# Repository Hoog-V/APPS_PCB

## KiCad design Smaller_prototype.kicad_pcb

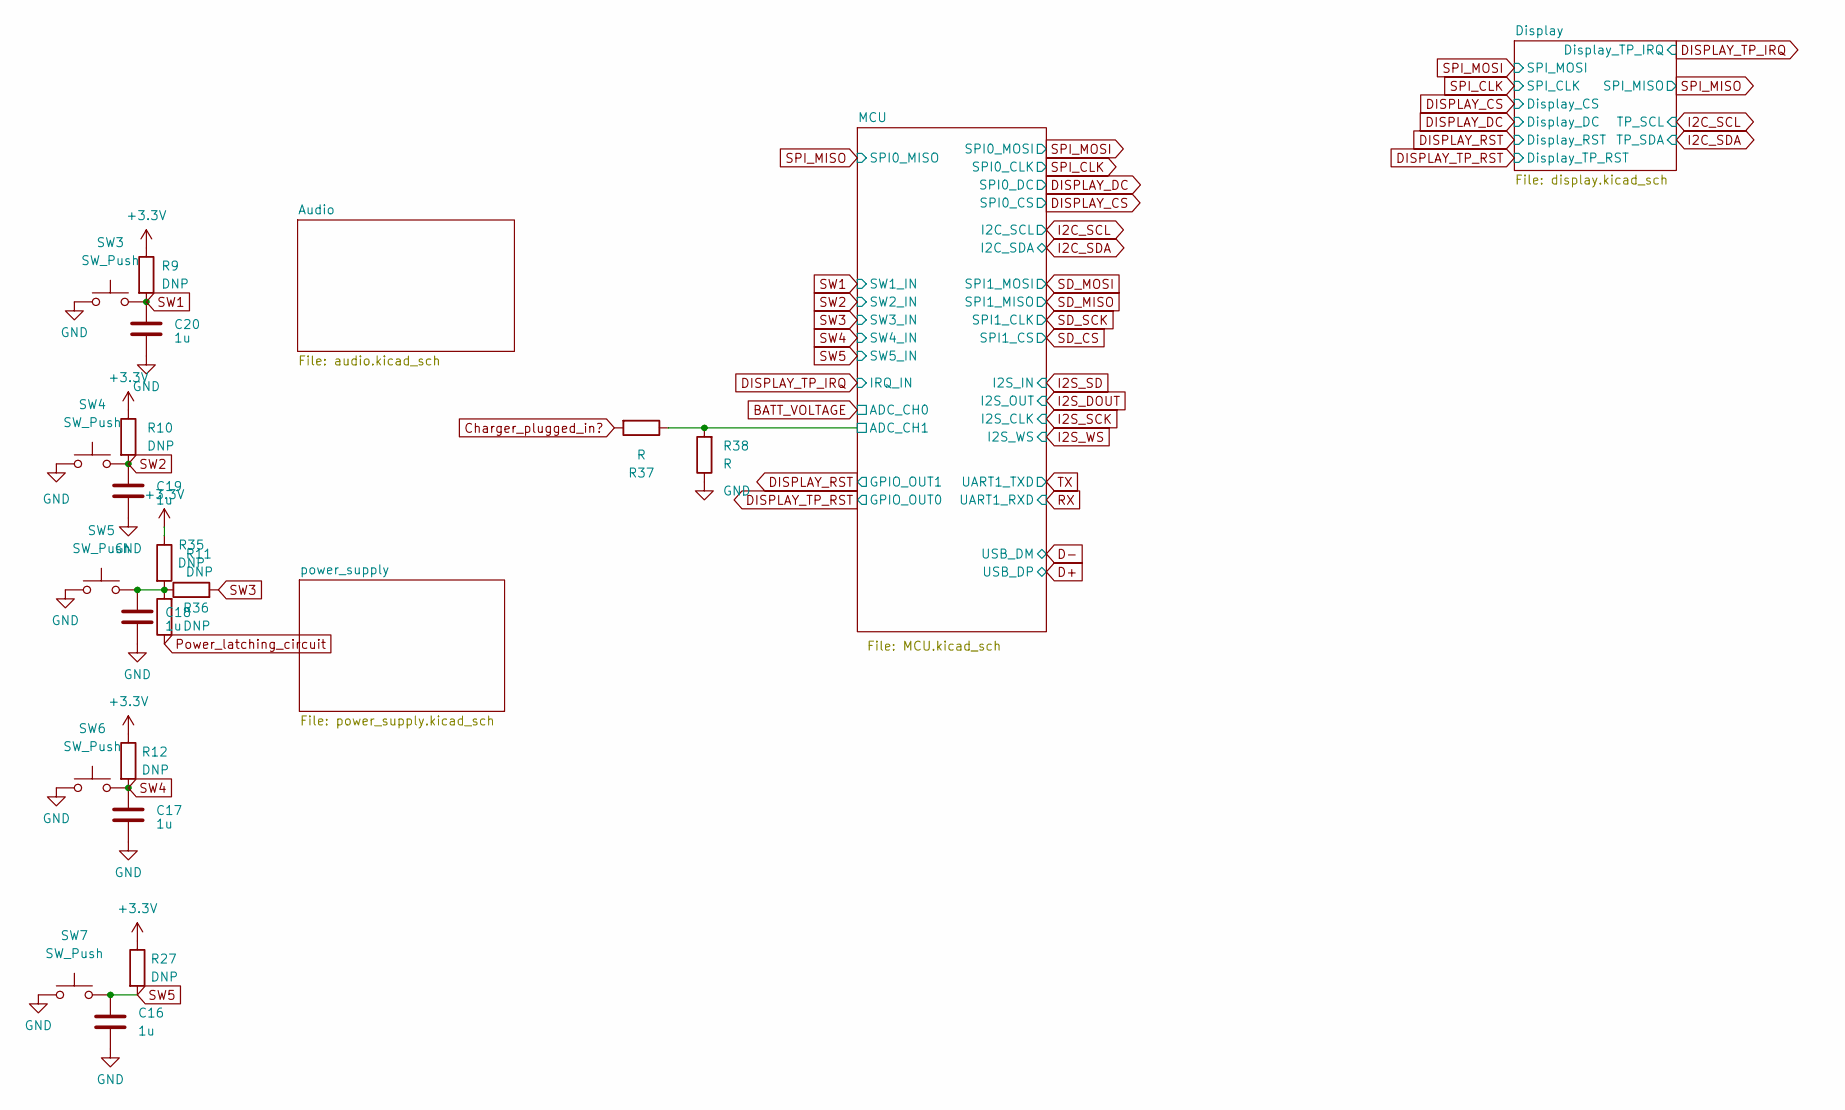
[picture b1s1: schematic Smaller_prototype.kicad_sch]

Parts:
C16, C17, C18, C19, C20: 1u; C_0603_1608Metric_Pad1.08x0.95mm_HandSolder
R9, R10, R11, R12, R27, R35, R36: DNP; R_0603_1608Metric_Pad0.98x0.95mm_HandSolder
R37, R38: R; R_0603_1608Metric_Pad0.98x0.95mm_HandSolder
SW3, SW4, SW5, SW6, SW7: SW_Push; SW_SPST_B3S-1000

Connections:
+3.3V: R9.1, R10.1, R11.1, R12.1, R27.1; also elsewhere on the board
/MCU/ADC_CH1: R37.1, R38.2; also elsewhere on the board
Charger_plugged_in?: R37.2; also elsewhere on the board
GND: C16.2, C17.2, C18.2, C19.2, C20.2, R38.1, SW3.1, SW4.1, SW5.1, SW6.1, SW7.1; also elsewhere on the board
unnamed: C18.1, R11.2, R35.1, R36.2, SW5.2
Power_latching_circuit: R36.1; also elsewhere on the board
SW1: C20.1, R9.2, SW3.2; also elsewhere on the board
SW2: C19.1, R10.2, SW4.2; also elsewhere on the board
SW3: R35.2; also elsewhere on the board
SW4: C17.1, R12.2, SW6.2; also elsewhere on the board
SW5: C16.1, R27.2, SW7.2; also elsewhere on the board

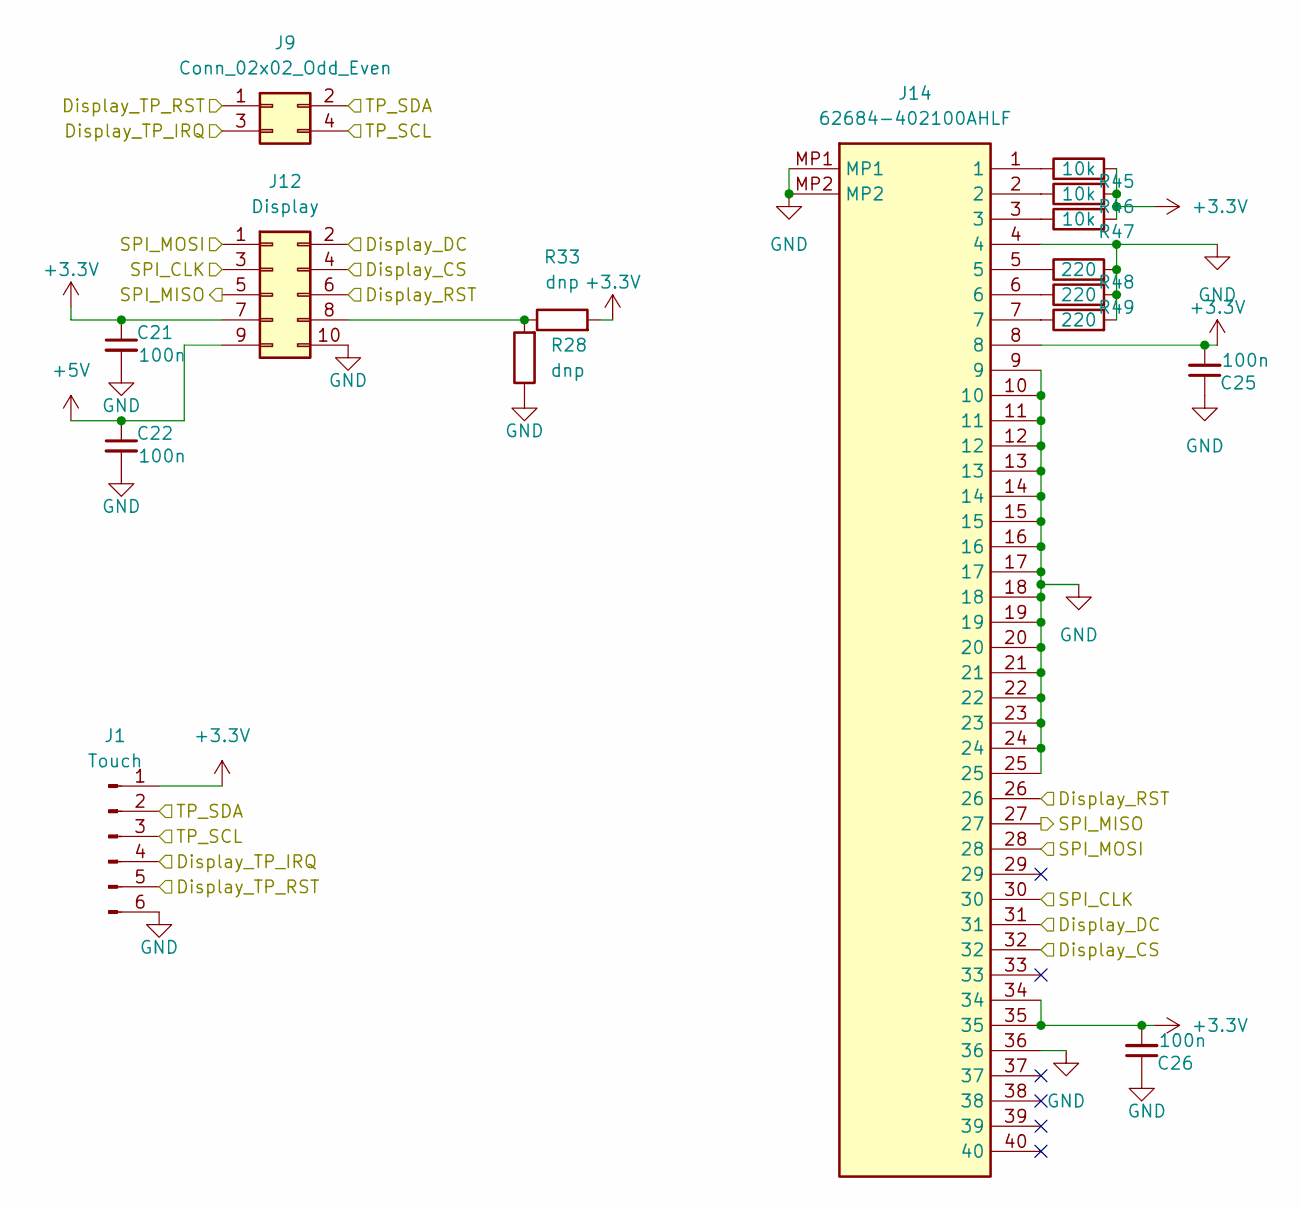
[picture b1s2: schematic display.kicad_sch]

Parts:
C21, C22, C25, C26: 100n; C_0603_1608Metric_Pad1.08x0.95mm_HandSolder
J1: Touch; TE_0-1734839-6_1x06-1MP_P0.5mm_Horizontal
J9: Conn_02x02_Odd_Even; PinHeader_2x02_P2.54mm_Vertical_SMD
J12: Display; PinHeader_2x05_P2.54mm_Vertical_SMD
J14: 62684-402100AHLF; 62684402100AHLF; Manufacturer_Part_Number 62684-402100AHLF
R28, R33: dnp; R_0603_1608Metric_Pad0.98x0.95mm_HandSolder
R45, R46, R47: 10k; R_0603_1608Metric_Pad0.98x0.95mm_HandSolder
R48, R49, R50: 220; R_0603_1608Metric_Pad0.98x0.95mm_HandSolder

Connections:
+3.3V: C21.1, C25.2, C26.2, J1.1, J12.7, J14.8, J14.34, J14.35, R33.2, R45.2, R46.2, R47.2; also elsewhere on the board
+5V: C22.1, J12.9; also elsewhere on the board
DISPLAY_CS: J12.4, J14.32; also elsewhere on the board
DISPLAY_DC: J12.2, J14.31; also elsewhere on the board
DISPLAY_RST: J12.6, J14.26; also elsewhere on the board
DISPLAY_TP_IRQ: J1.4, J9.3; also elsewhere on the board
DISPLAY_TP_RST: J1.5, J9.1; also elsewhere on the board
GND: C21.2, C22.2, C25.1, C26.1, J1.6, J12.10, J14.4, J14.9, J14.10, J14.11, J14.12, J14.13, J14.14, J14.15, J14.16, J14.17, J14.18, J14.19, J14.20, J14.21, J14.22, J14.23, J14.24, J14.25, J14.36, J14.MP1, J14.MP2, R28.1, R48.2, R49.2, R50.2; also elsewhere on the board
I2C_SCL: J1.3, J9.4; also elsewhere on the board
I2C_SDA: J1.2, J9.2; also elsewhere on the board
unnamed: J12.8, R28.2, R33.1
unnamed: J14.1, R45.1
unnamed: J14.2, R46.1
unnamed: J14.3, R47.1
unnamed: J14.5, R48.1
unnamed: J14.6, R49.1
unnamed: J14.7, R50.1
SPI_CLK: J12.3, J14.30; also elsewhere on the board
SPI_MISO: J12.5, J14.27; also elsewhere on the board
SPI_MOSI: J12.1, J14.28; also elsewhere on the board

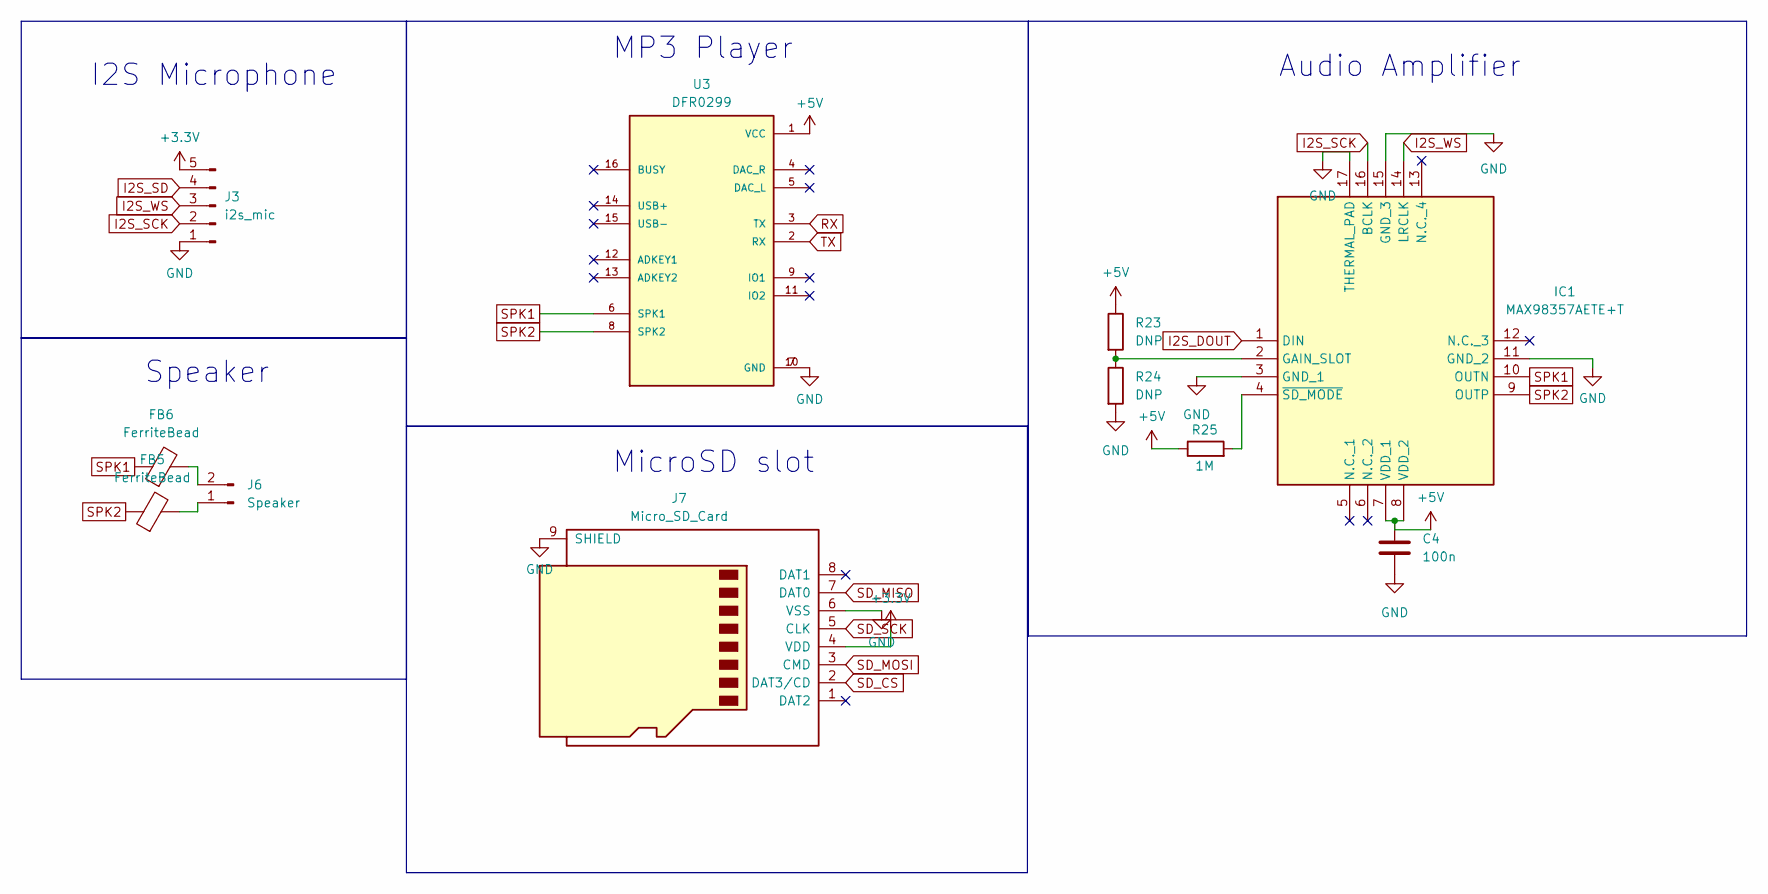
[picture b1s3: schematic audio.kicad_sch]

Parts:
C4: 100n; C_0603_1608Metric_Pad1.08x0.95mm_HandSolder
FB5, FB6: FerriteBead; R_1812_4532Metric
IC1: MAX98357AETE+T; QFN50P300X300X80-17N; Mouser Part Number 700-MAX98357AETE+T
J3: i2s_mic; PinHeader_1x05_P2.54mm_Vertical
J6: Speaker; PinHeader_1x02_P2.54mm_Vertical
J7: Micro_SD_Card; microSD_HC_Molex_47219-2001
R23, R24: DNP; R_0603_1608Metric_Pad0.98x0.95mm_HandSolder
R25: 1M; R_0603_1608Metric_Pad0.98x0.95mm_HandSolder
U3: DFR0299; DFPlayer_V2

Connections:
+3.3V: J3.5, J7.4 (VDD); also elsewhere on the board
+5V: C4.1, IC1.7 (VDD_1), IC1.8 (VDD_2), R23.1, R25.1, U3.1 (VCC); also elsewhere on the board
GND: C4.2, IC1.3 (GND_1), IC1.11 (GND_2), IC1.15 (GND_3), IC1.17 (THERMAL_PAD), J3.1, J7.6 (VSS), J7.9 (SHIELD), R24.2, U3.7 (GND), U3.10 (GND); also elsewhere on the board
I2S_DOUT: IC1.1 (DIN); also elsewhere on the board
I2S_SCK: IC1.16 (BCLK), J3.2; also elsewhere on the board
I2S_SD: J3.4; also elsewhere on the board
I2S_WS: IC1.14 (LRCLK), J3.3; also elsewhere on the board
unnamed: IC1.2 (GAIN_SLOT), R23.2, R24.1
unnamed: IC1.4 (~SD_MODE), R25.2
unnamed: FB5.2, J6.1
unnamed: FB6.2, J6.2
RX: U3.3 (TX); also elsewhere on the board
SD_CS: J7.2 (DAT3/CD); also elsewhere on the board
SD_MISO: J7.7 (DAT0); also elsewhere on the board
SD_MOSI: J7.3 (CMD); also elsewhere on the board
SD_SCK: J7.5 (CLK); also elsewhere on the board
SPK1: FB6.1, IC1.10 (OUTN), U3.6 (SPK1)
SPK2: FB5.1, IC1.9 (OUTP), U3.8 (SPK2)
TX: U3.2 (RX); also elsewhere on the board

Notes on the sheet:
Speaker
MP3 Player
I2S Microphone
Audio Amplifier
MicroSD slot

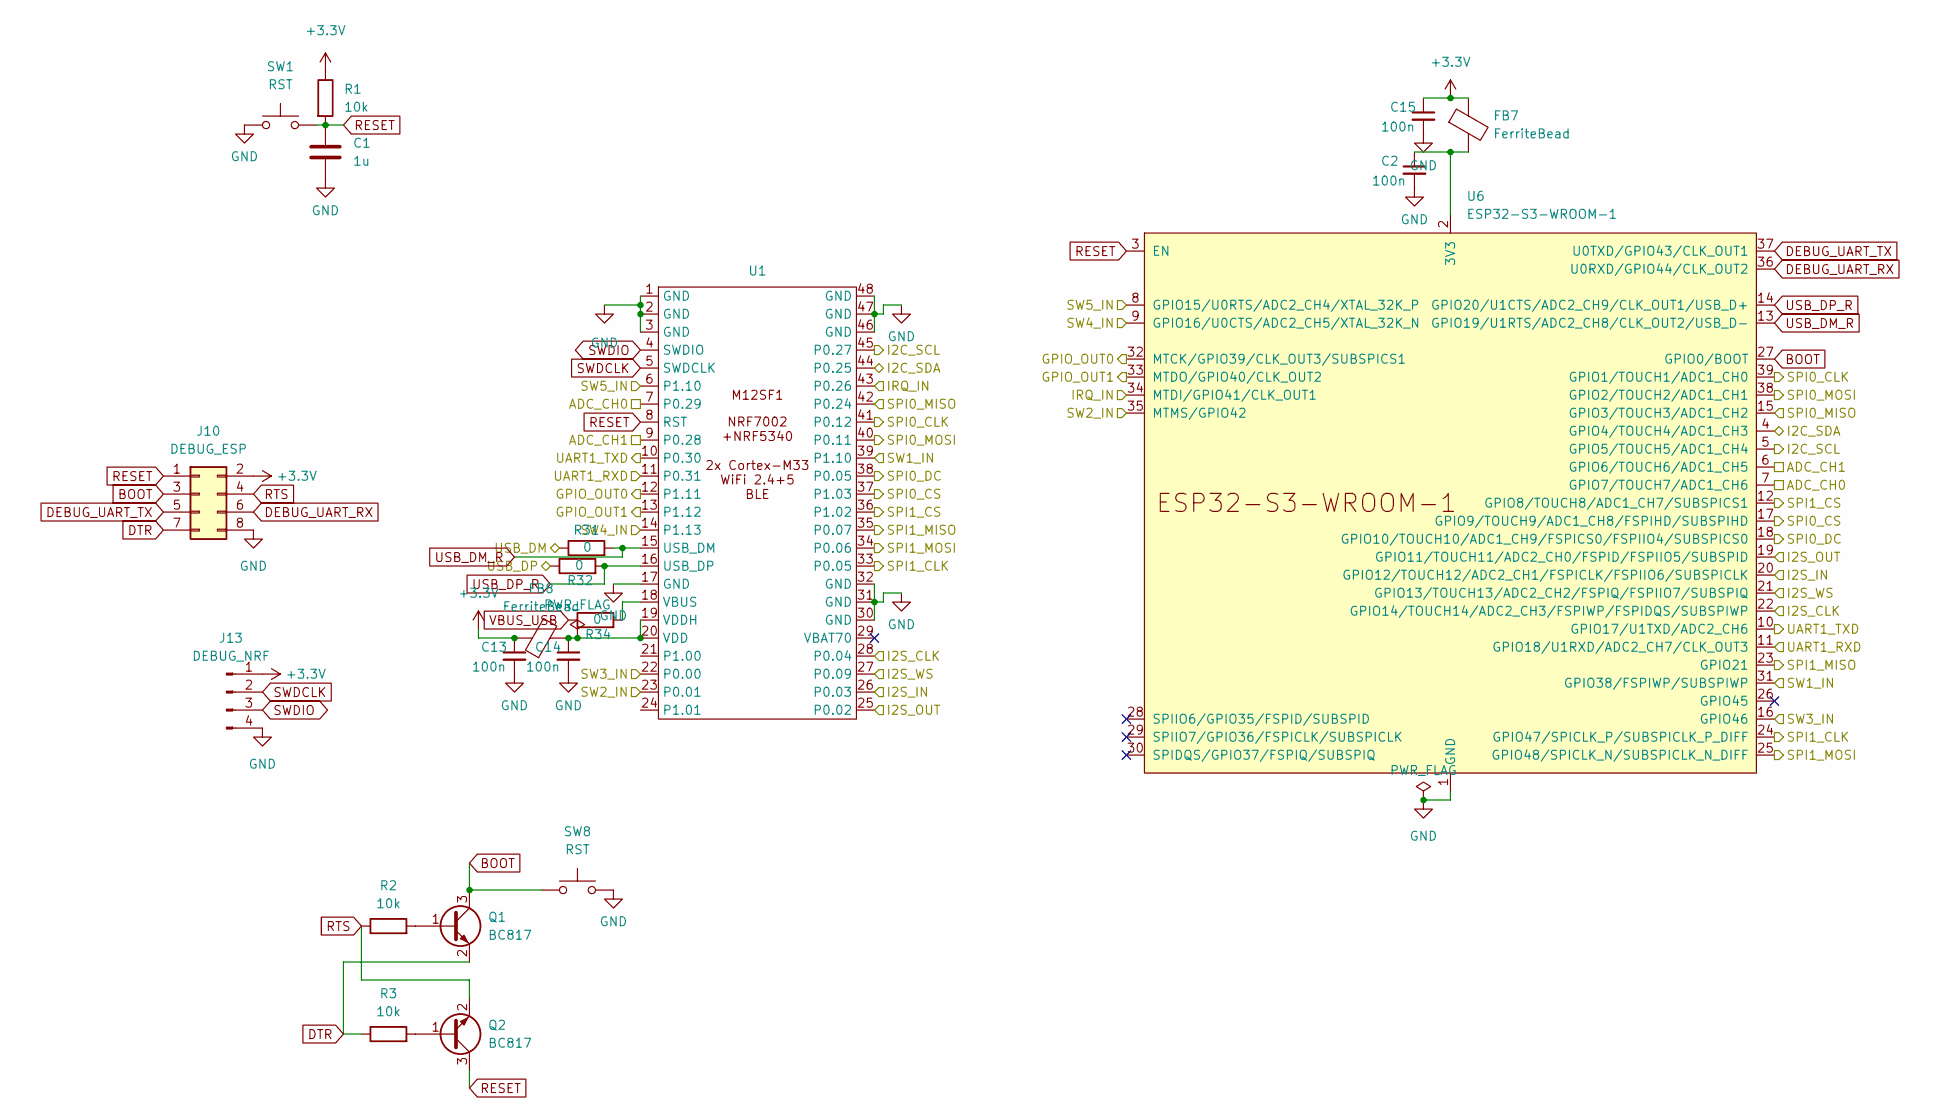
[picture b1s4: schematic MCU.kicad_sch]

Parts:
C1: 1u; C_0603_1608Metric_Pad1.08x0.95mm_HandSolder
C2, C13, C14, C15: 100n; C_0603_1608Metric_Pad1.08x0.95mm_HandSolder
FB7, FB8: FerriteBead; R_1812_4532Metric
J10: DEBUG_ESP; PinHeader_2x04_P2.54mm_Vertical_SMD
J13: DEBUG_NRF; PinHeader_2x02_P2.54mm_Vertical_SMD
Q1, Q2: BC817; SOT-23
R1, R2, R3: 10k; R_0603_1608Metric_Pad0.98x0.95mm_HandSolder
R31, R32, R34: 0; R_0603_1608Metric_Pad0.98x0.95mm_HandSolder
SW1, SW8: RST; SW_SPST_B3S-1000
U1: M12SF1
U6: ESP32-S3-WROOM-1

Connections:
+3.3V: C13.1, C15.1, FB7.1, FB8.1, J10.2, J13.1, R1.1; also elsewhere on the board
/MCU/ADC_CH1: U1.9 (P0.28), U6.6 (GPIO6/TOUCH6/ADC1_CH5); also elsewhere on the board
BATT_VOLTAGE: U1.7 (P0.29), U6.7 (GPIO7/TOUCH7/ADC1_CH6); also elsewhere on the board
BOOT: J10.3, Q1.3 (C), SW8.1, U6.27 (GPIO0/BOOT)
D+: R32.1; also elsewhere on the board
D-: R31.1; also elsewhere on the board
DEBUG_UART_RX: J10.6, U6.36 (U0RXD/GPIO44/CLK_OUT2)
DEBUG_UART_TX: J10.5, U6.37 (U0TXD/GPIO43/CLK_OUT1)
DISPLAY_CS: U1.37 (P1.03), U6.17 (GPIO9/TOUCH9/ADC1_CH8/FSPIHD/SUBSPIHD); also elsewhere on the board
DISPLAY_DC: U1.38 (P0.05), U6.18 (GPIO10/TOUCH10/ADC1_CH9/FSPICS0/FSPIIO4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); also elsewhere on the board
DISPLAY_RST: U1.13 (P1.12), U6.33 (MTDO/GPIO40/CLK_OUT2); also elsewhere on the board
DISPLAY_TP_IRQ: U1.43 (P0.26), U6.34 (MTDI/GPIO41/CLK_OUT1); also elsewhere on the board
DISPLAY_TP_RST: U1.12 (P1.11), U6.32 (MTCK/GPIO39/CLK_OUT3/SUBSPICS1); also elsewhere on the board
DTR: J10.7, Q1.2 (E), R3.1
GND: C1.2, C2.2, C13.2, C14.2, C15.2, J10.8, J13.4, SW1.1, SW8.2, U1.1 (GND), U1.2 (GND), U1.3 (GND), U1.17 (GND), U1.30 (GND), U1.31 (GND), U1.32 (GND), U1.46 (GND), U1.47 (GND), U1.48 (GND), U6.1 (GND), U6.40 (GND), U6.41 (GND); also elsewhere on the board
I2C_SCL: U1.45 (P0.27), U6.5 (GPIO5/TOUCH5/ADC1_CH4); also elsewhere on the board
I2C_SDA: U1.44 (P0.25), U6.4 (GPIO4/TOUCH4/ADC1_CH3); also elsewhere on the board
I2S_DOUT: U1.25 (P0.02), U6.19 (GPIO11/TOUCH11/ADC2_CH0/FSPID/FSPIIO5/S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); also elsewhere on the board
I2S_SCK: U1.28 (P0.04), U6.22 (GPIO14/TOUCH14/ADC2_CH3/FSPIWP/FSPIDQS/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); also elsewhere on the board
I2S_SD: U1.26 (P0.03), U6.20 (GPIO12/TOUCH12/ADC2_CH1/FSPICLK/FSPIIO6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); also elsewhere on the board
I2S_WS: U1.27 (P0.09), U6.21 (GPIO13/TOUCH13/ADC2_CH2/FSPIQ/FSPIIO7/S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); also elsewhere on the board
unnamed: Q1.1 (B), R2.2
unnamed: Q2.1 (B), R3.2
unnamed: R34.2, U1.18 (VBUS)
unnamed: C14.1, FB8.2, U1.19 (VDDH), U1.20 (VDD)
unnamed: C2.1, FB7.2, U6.2 (3V3)
RESET: C1.1, J10.1, Q2.3 (C), R1.2, SW1.2, U1.8 (RST), U6.3 (EN)
RTS: J10.4, Q2.2 (E), R2.1
RX: U1.11 (P0.31), U6.11 (GPIO18/U1RXD/ADC2_CH7/CLK_OUT3); also elsewhere on the board
SD_CS: U1.36 (P1.02), U6.12 (GPIO8/TOUCH8/ADC1_CH7/SUBSPICS1); also elsewhere on the board
SD_MISO: U1.35 (P0.07), U6.23 (GPIO21); also elsewhere on the board
SD_MOSI: U1.34 (P0.06), U6.25 (GPIO48/SPICLK_N/SUBSPICLK_N_DIFF); also elsewhere on the board
SD_SCK: U1.33 (P0.05), U6.24 (GPIO47/SPICLK_P/SUBSPICLK_P_DIFF); also elsewhere on the board
SPI_CLK: U1.41 (P0.12), U6.39 (GPIO1/TOUCH1/ADC1_CH0); also elsewhere on the board
SPI_MISO: U1.42 (P0.24), U6.15 (GPIO3/TOUCH3/ADC1_CH2); also elsewhere on the board
SPI_MOSI: U1.40 (P0.11), U6.38 (GPIO2/TOUCH2/ADC1_CH1); also elsewhere on the board
SW1: U1.39 (P1.10), U6.31 (GPIO38/FSPIWP/SUBSPIWP); also elsewhere on the board
SW2: U1.23 (P0.01), U6.35 (MTMS/GPIO42); also elsewhere on the board
SW3: U1.22 (P0.00), U6.16 (GPIO46); also elsewhere on the board
SW4: U1.14 (P1.13), U6.9 (GPIO16/U0CTS/ADC2_CH5/XTAL_32K_N); also elsewhere on the board
SW5: U1.6 (P1.10), U6.8 (GPIO15/U0RTS/ADC2_CH4/XTAL_32K_P); also elsewhere on the board
SWDCLK: J13.2, U1.5 (SWDCLK)
SWDIO: J13.3, U1.4 (SWDIO)
TX: U1.10 (P0.30), U6.10 (GPIO17/U1TXD/ADC2_CH6); also elsewhere on the board
USB_DM_R: R31.2, U1.15 (USB_DM), U6.13 (GPIO19/U1RTS/ADC2_CH8/CLK_OUT2/USB_D-)
USB_DP_R: R32.2, U1.16 (USB_DP), U6.14 (GPIO20/U1CTS/ADC2_CH9/CLK_OUT1/USB_D+)
VBUS_USB: R34.1; also elsewhere on the board

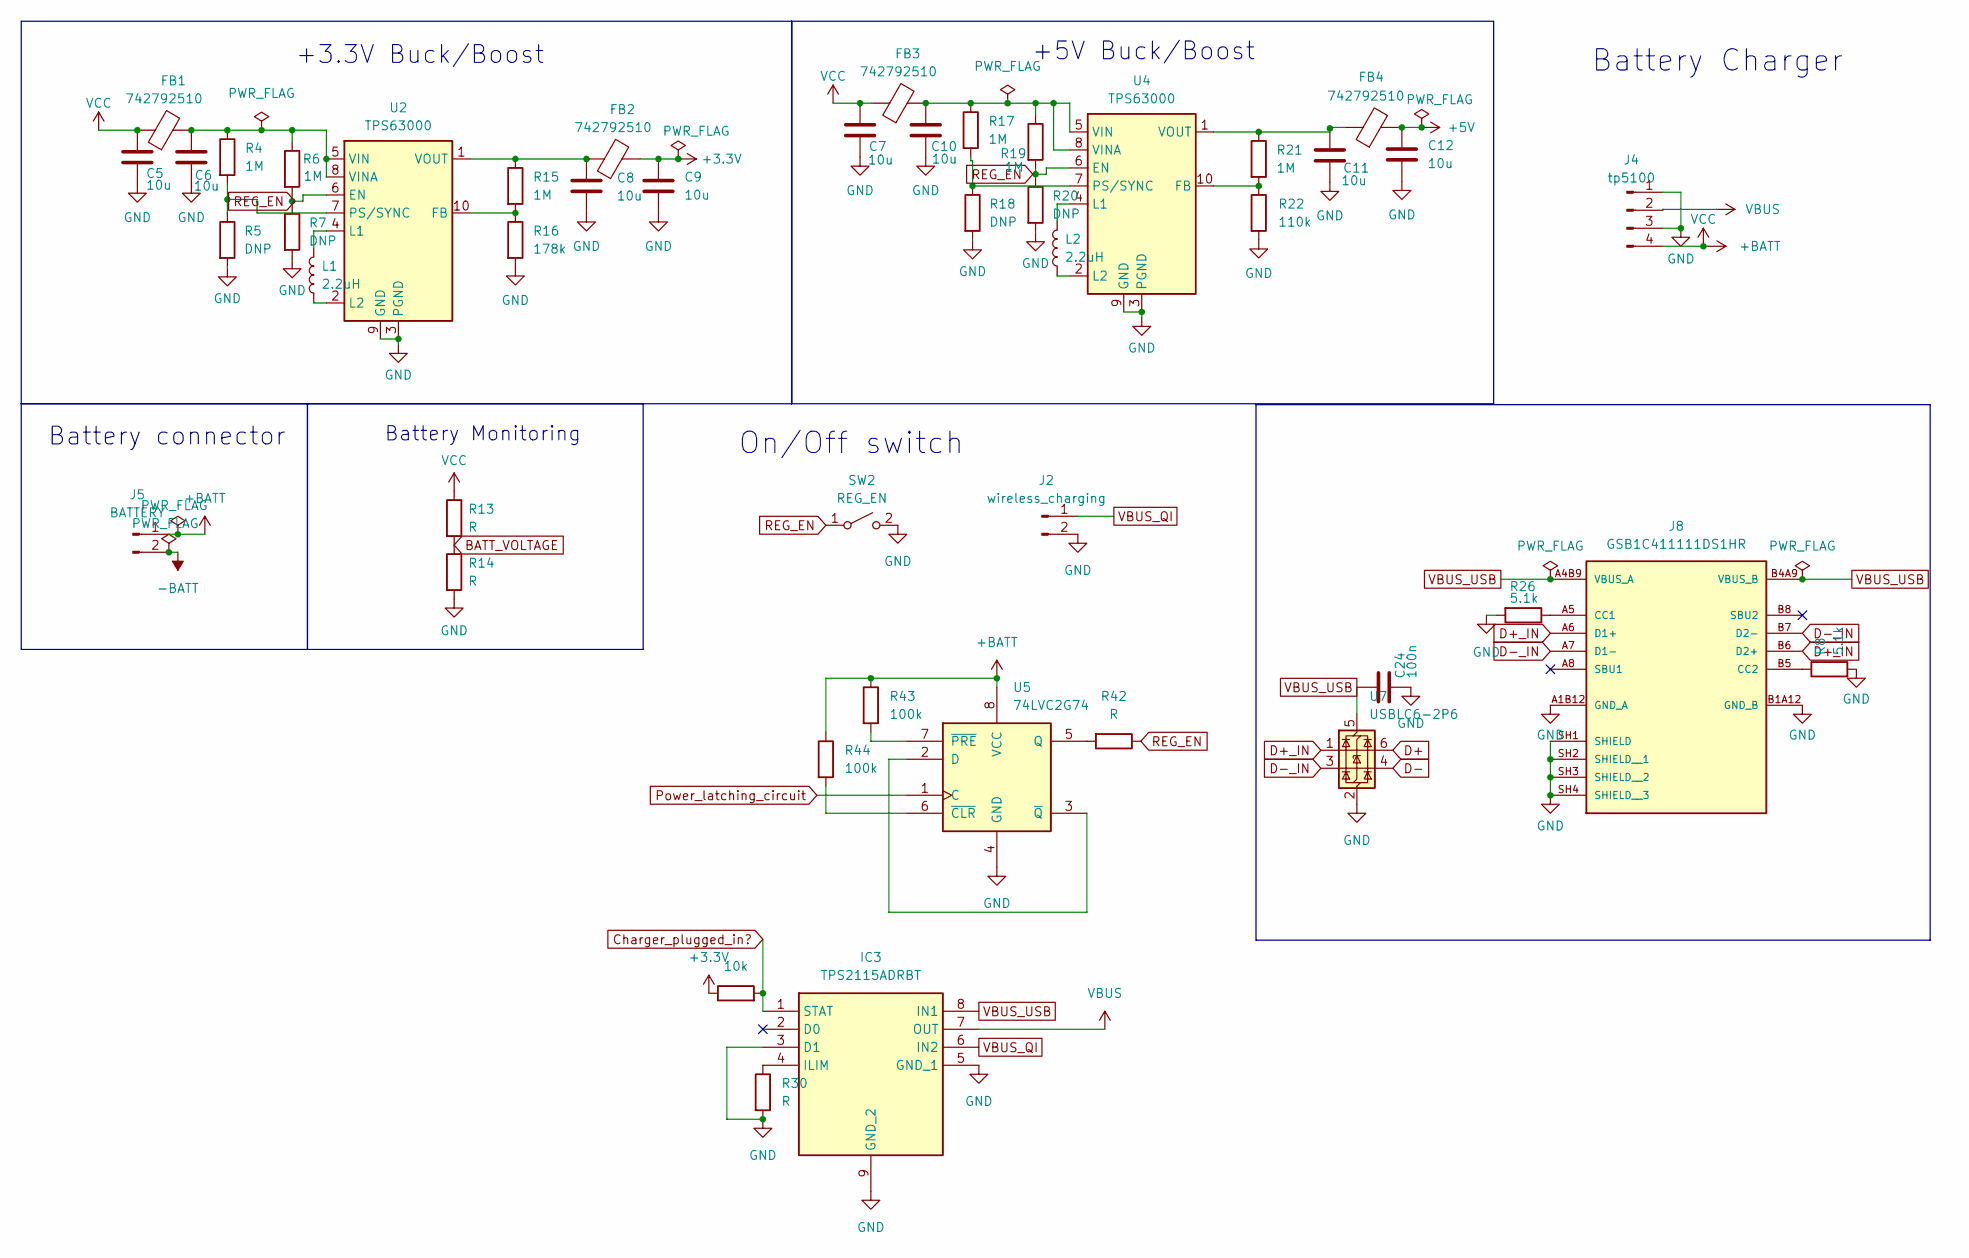
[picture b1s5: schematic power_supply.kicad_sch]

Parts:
C5, C6, C7, C8, C9, C10, C11, C12: 10u; C_0603_1608Metric_Pad1.08x0.95mm_HandSolder
C24: 100n; C_0603_1608Metric_Pad1.08x0.95mm_HandSolder
FB1, FB2, FB3, FB4: 742792510; R_1812_4532Metric
IC3: TPS2115ADRBT; SON65P300X300X100-9N-D; Mouser Part Number 595-TPS2115ADRBT
J2: wireless_charging; PinHeader_1x02_P2.54mm_Horizontal
J4: tp5100
J5: BATTERY; PinHeader_1x02_P2.54mm_Vertical
J8: GSB1C411111DS1HR; AMPHENOL_GSB1C411111DS1HR; PARTREV AX3
L1, L2: 2.2uH; INDC3225X120N
R4, R6, R15, R17, R19, R21: 1M; R_0603_1608Metric_Pad0.98x0.95mm_HandSolder
R5, R7, R18, R20: DNP; R_0603_1608Metric_Pad0.98x0.95mm_HandSolder
R8, R26: 5.1k; R_0603_1608Metric_Pad0.98x0.95mm_HandSolder
R13, R14, R30, R42: R; R_0603_1608Metric_Pad0.98x0.95mm_HandSolder
R16: 178k; R_0603_1608Metric_Pad0.98x0.95mm_HandSolder
R22: 110k; R_0603_1608Metric_Pad0.98x0.95mm_HandSolder
R29: 10k; R_0603_1608Metric_Pad0.98x0.95mm_HandSolder
R43, R44: 100k; R_0603_1608Metric_Pad0.98x0.95mm_HandSolder
SW2: REG_EN; SW_Slide_SPDT_Angled_CK_OS102011MA1Q
U2, U4: TPS63000; Texas_DRC0010J_ThermalVias
U5: 74LVC2G74; TSSOP-8_3x3mm_P0.65mm
U7: USBLC6-2P6; SOT-666

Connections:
+3.3V: C9.1, FB2.2, R29.1; also elsewhere on the board
+5V: C12.1, FB4.2; also elsewhere on the board
+BATT: C5.1, C7.1, FB1.1, FB3.1, J4.4, J5.1, R13.1, R43.1, R44.1, U5.8 (VCC)
-BATT: J5.2
BATT_VOLTAGE: R13.2, R14.1; also elsewhere on the board
Charger_plugged_in?: IC3.1 (STAT), R29.2; also elsewhere on the board
D+: U7.6 (I/O1); also elsewhere on the board
D+_IN: J8.A6 (D1+), J8.B6 (D2+), U7.1 (I/O1)
D-: U7.4 (I/O2); also elsewhere on the board
D-_IN: J8.A7 (D1-), J8.B7 (D2-), U7.3 (I/O2)
GND: C5.2, C6.2, C7.2, C8.2, C9.2, C10.2, C11.2, C12.2, C24.2, IC3.3 (D1), IC3.5 (GND_1), IC3.9 (GND_2), J2.2, J4.1, J4.3, J8.A1B12 (GND_A), J8.B1A12 (GND_B), J8.SH1 (SHIELD), J8.SH2 (SHIELD__1), J8.SH3 (SHIELD__2), J8.SH4 (SHIELD__3), R5.2, R7.2, R8.2, R14.2, R16.2, R18.2, R20.2, R22.2, R26.2, R30.2, SW2.2 (B), U2.3 (PGND), U2.9 (GND), U2.11 (PGND), U4.3 (PGND), U4.9 (GND), U4.11 (PGND), U5.4 (GND), U7.2 (GND); also elsewhere on the board
unnamed: IC3.4 (ILIM), R30.1
unnamed: J8.A5 (CC1), R26.1
unnamed: J8.B5 (CC2), R8.1
unnamed: R15.2, R16.1, U2.10 (FB)
unnamed: L1.2, U2.4 (L1)
unnamed: L1.1, U2.2 (L2)
unnamed: R4.2, R5.1, U2.7 (PS/SYNC)
unnamed: C6.1, FB1.2, R4.1, R6.1, U2.5 (VIN), U2.8 (VINA)
unnamed: C8.1, FB2.1, R15.1, U2.1 (VOUT)
unnamed: R21.2, R22.1, U4.10 (FB)
unnamed: L2.2, U4.4 (L1)
unnamed: L2.1, U4.2 (L2)
unnamed: R17.2, R18.1, U4.7 (PS/SYNC)
unnamed: C10.1, FB3.2, R17.1, R19.1, U4.5 (VIN), U4.8 (VINA)
unnamed: C11.1, FB4.1, R21.1, U4.1 (VOUT)
unnamed: U5.2 (D), U5.3 (~Q)
unnamed: R42.2, U5.5 (Q)
unnamed: R44.2, U5.6 (~CLR)
unnamed: R43.2, U5.7 (~PRE)
Power_latching_circuit: U5.1 (C); also elsewhere on the board
REG_EN: R6.2, R7.1, R19.2, R20.1, R42.1, SW2.1 (A), U2.6 (EN), U4.6 (EN)
VBUS: IC3.7 (OUT), J4.2
VBUS_QI: IC3.6 (IN2), J2.1
VBUS_USB: C24.1, IC3.8 (IN1), J8.A4B9 (VBUS_A), J8.B4A9 (VBUS_B), U7.5 (VBUS); also elsewhere on the board

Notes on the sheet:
+3.3V Buck/Boost
Battery Charger
Battery Monitoring
On/Off switch
+5V Buck/Boost
Battery connector

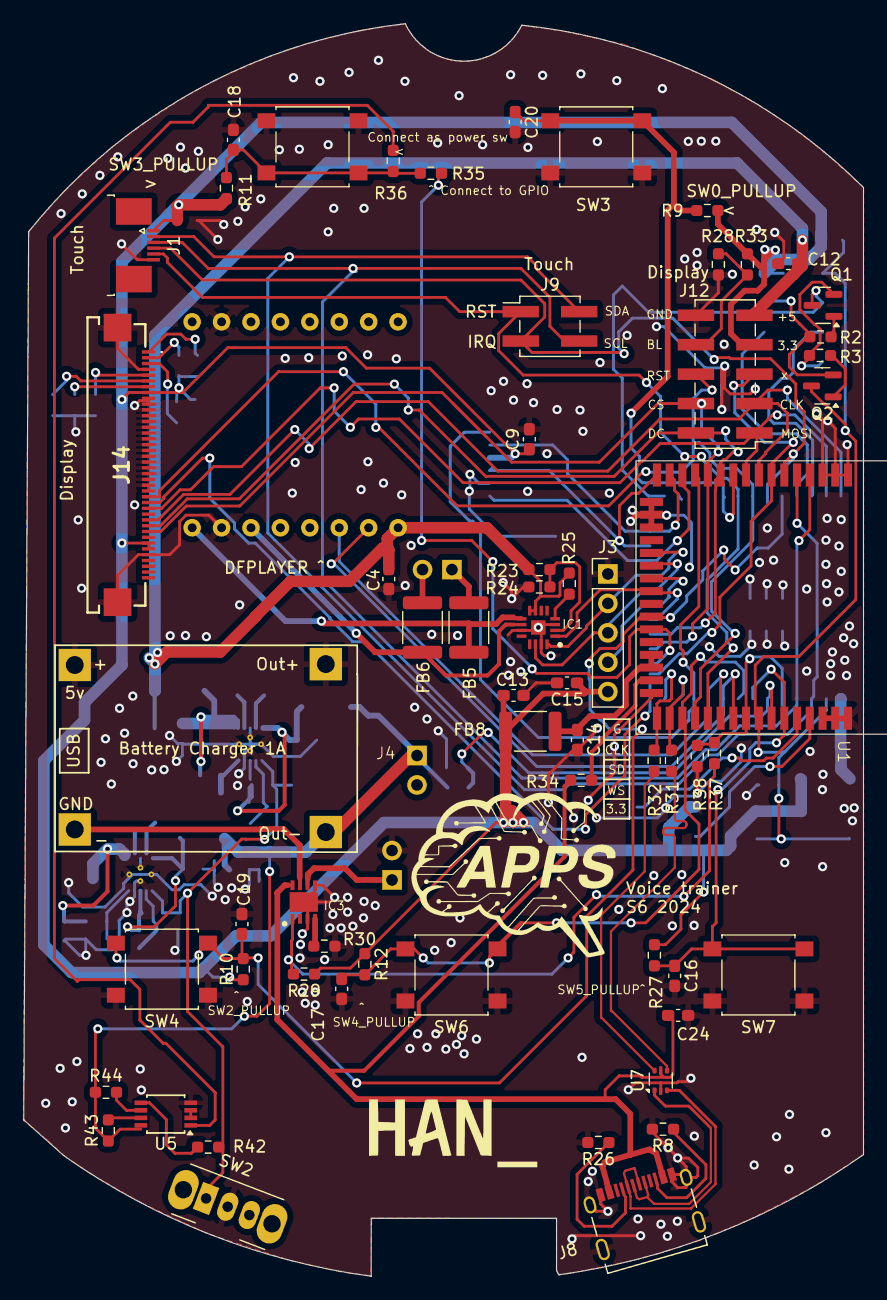
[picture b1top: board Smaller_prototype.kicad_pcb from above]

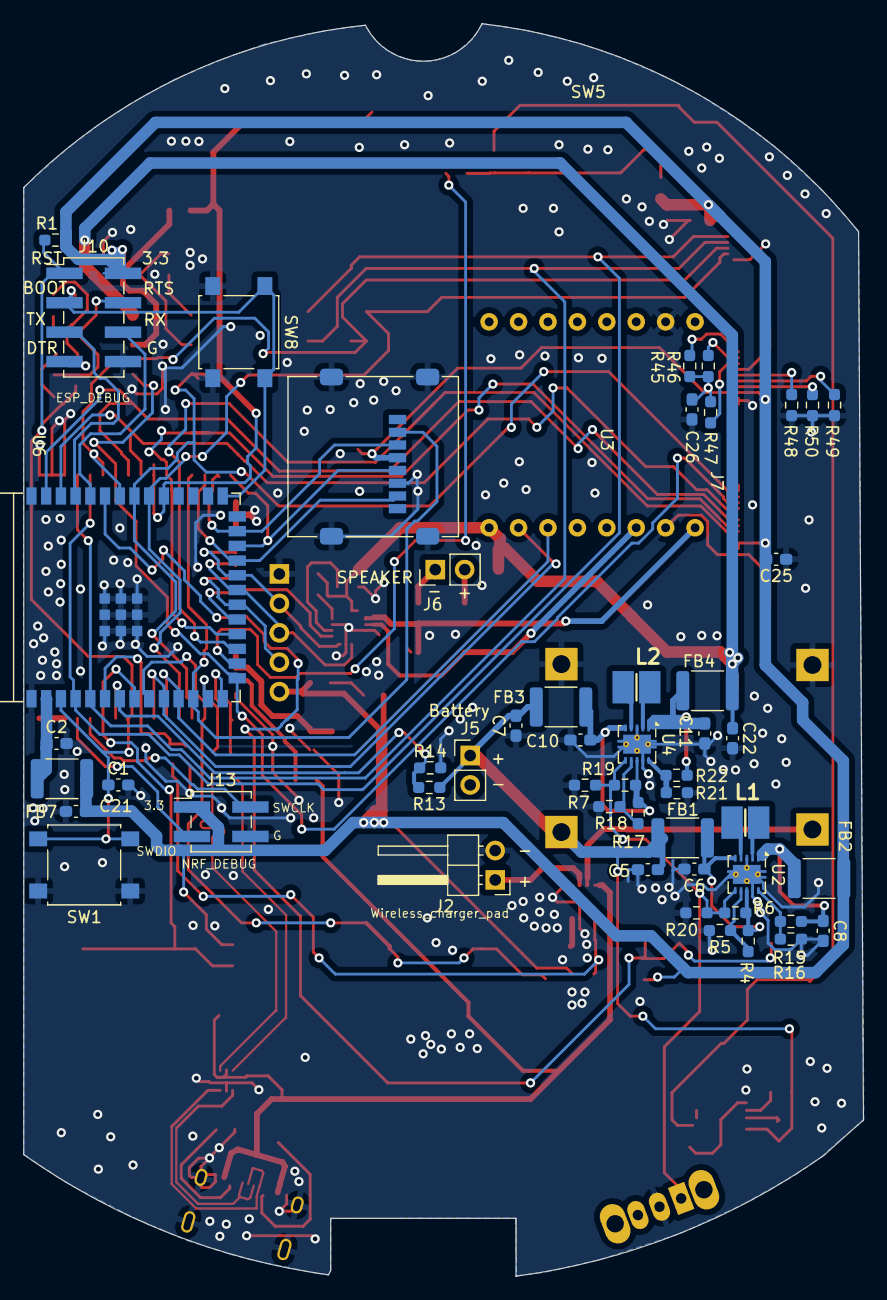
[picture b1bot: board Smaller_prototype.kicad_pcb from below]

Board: 2 copper layers, 72.5 x 108.1 mm, 113 parts (52 on the bottom side), 89 nets.

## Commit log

2024-05-19 -add first revision of schematic
2024-05-27 -add some changes to power section and display
2024-05-27 -enh repin mcu in schematic
2024-05-29 -add soft latching circuit, routing mostly done
2024-05-30 -add end revision
